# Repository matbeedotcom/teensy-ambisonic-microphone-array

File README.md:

# Teensy Ambisonic Microphone Array

A real-time 3D audio capture and direction-of-arrival (DOA) system using Teensy 4.1 and MEMS microphones.

## Overview

This project implements an 8-channel tetrahedral microphone array for spatial audio applications. Four INMP441 digital MEMS microphones capture sound from all directions, enabling real-time sound source localization with visual feedback.

### Key Features

- **8-channel audio capture** via dual Teensy 4.1 boards (master/slave configuration)
- **Real-time DOA estimation** using GCC-PHAT and SRP-PHAT algorithms
- **Sound classification** to filter and track specific audio types (voice, music, claps)
- **Live visualization** with 2D/3D directional plots and channel monitoring
- **3D-printable frame** with integrated wire management

## System Architecture

```
┌─────────────┐     I2S      ┌──────────────┐     USB Audio    ┌──────────────┐
│ 4x INMP441  ├─────────────►│ Master Teensy├────────────────►│              │
│ Microphones │              │     4.1      │                  │   Host PC    │
└─────────────┘              └──────┬───────┘                  │   (Python)   │
                                     │ TDM                      │              │
┌─────────────┐     I2S      ┌──────┴───────┐                  │ ┌──────────┐ │
│ 4x INMP441  ├─────────────►│ Slave Teensy │                  │ │   DOA    │ │
│ Microphones │              │     4.1      │                  │ │Processing│ │
└─────────────┘              └──────────────┘                  │ └──────────┘ │
                                                                └──────────────┘
```

## Hardware Requirements

- 2× Teensy 4.1 boards
- 8× INMP441 I2S MEMS microphone breakout boards
- 3D printer for tetrahedral frame (70.7mm edge length)
- Wire for I2S and TDM connections
- USB cables for power and data

## Quick Start

### 1. Assemble Hardware

Print the tetrahedral frame and mount microphones:
```bash
cd mechanical
python generate_stl.py  # Creates STL files for 3D printing
```

Follow the [assembly guide](mechanical/assembly_instructions.md) for wiring details.

### 2. Flash Firmware

Upload firmware to both Teensy boards:
- **Master**: `teensy_src/teensy_ambisonic_microphone.ino`
- **Slave**: `teensy_src/slave.ino`

Note: Requires [Teensyduino](https://www.pjrc.com/teensy/teensyduino.html) with USB descriptor patches from `teensy_src/patches/`.

### 3. Install Host Software

```bash
cd host_src
pip install -r requirements.txt
```

### 4. Run DOA Visualization

```bash
python doa_visualizer.py
```

Click "Start" to begin real-time sound source tracking.

## Features in Detail

### Direction of Arrival Algorithms

- **GCC-PHAT**: Fast cross-correlation for time-delay estimation
- **SRP-PHAT**: Robust beamforming-based localization
- **Least-Squares**: Traditional triangulation from time differences

### Sound Classification

Automatically identifies and filters:
- Human voice
- Music
- Claps/transients
- Whistles
- Background noise

### Array Geometry

Regular tetrahedron configuration:
- 43.3mm radius (center to vertex)
- 109.5° angular separation between microphones
- Omnidirectional coverage with minimal blind spots

## Project Structure

```
teensy_ambisonic_microphone/
├── teensy_src/        # Teensy firmware (master/slave)
├── host_src/          # Python DOA processing and visualization
├── mechanical/        # 3D-printable frame design (OpenSCAD)
└── pcb/              # KiCad PCB designs
```

## Performance

- **Sample rate**: 44.1 kHz
- **Latency**: ~23ms (1024 sample blocks)
- **Angular resolution**: 5° grid spacing
- **Update rate**: 20 Hz visualization
- **Maximum trackable distance**: Limited by SNR, typically 3-5 meters indoors

## Applications

- Acoustic scene analysis
- Smart home voice control
- Robotics navigation
- Virtual reality audio
- Acoustic research
- Educational demonstrations

## Contributing

Contributions welcome! Areas of interest:
- Multi-source tracking
- Beamforming implementation
- Raspberry Pi host support
- ROS integration

## License

MIT License - See LICENSE file for details

## Acknowledgments

Built with:
- [Teensy Audio Library](https://www.pjrc.com/teensy/td_libs_Audio.html)
- [INMP441 MEMS Microphones](https://invensense.tdk.com/products/digital/inmp441/)
- Scientific Python stack (NumPy, SciPy, Matplotlib)

## Resources

- [Direction of Arrival Estimation](https://en.wikipedia.org/wiki/Direction_of_arrival)
- [Ambisonic Audio](https://en.wikipedia.org/wiki/Ambisonics)
- [GCC-PHAT Algorithm](https://doi.org/10.1109/TASSP.1976.1162830)

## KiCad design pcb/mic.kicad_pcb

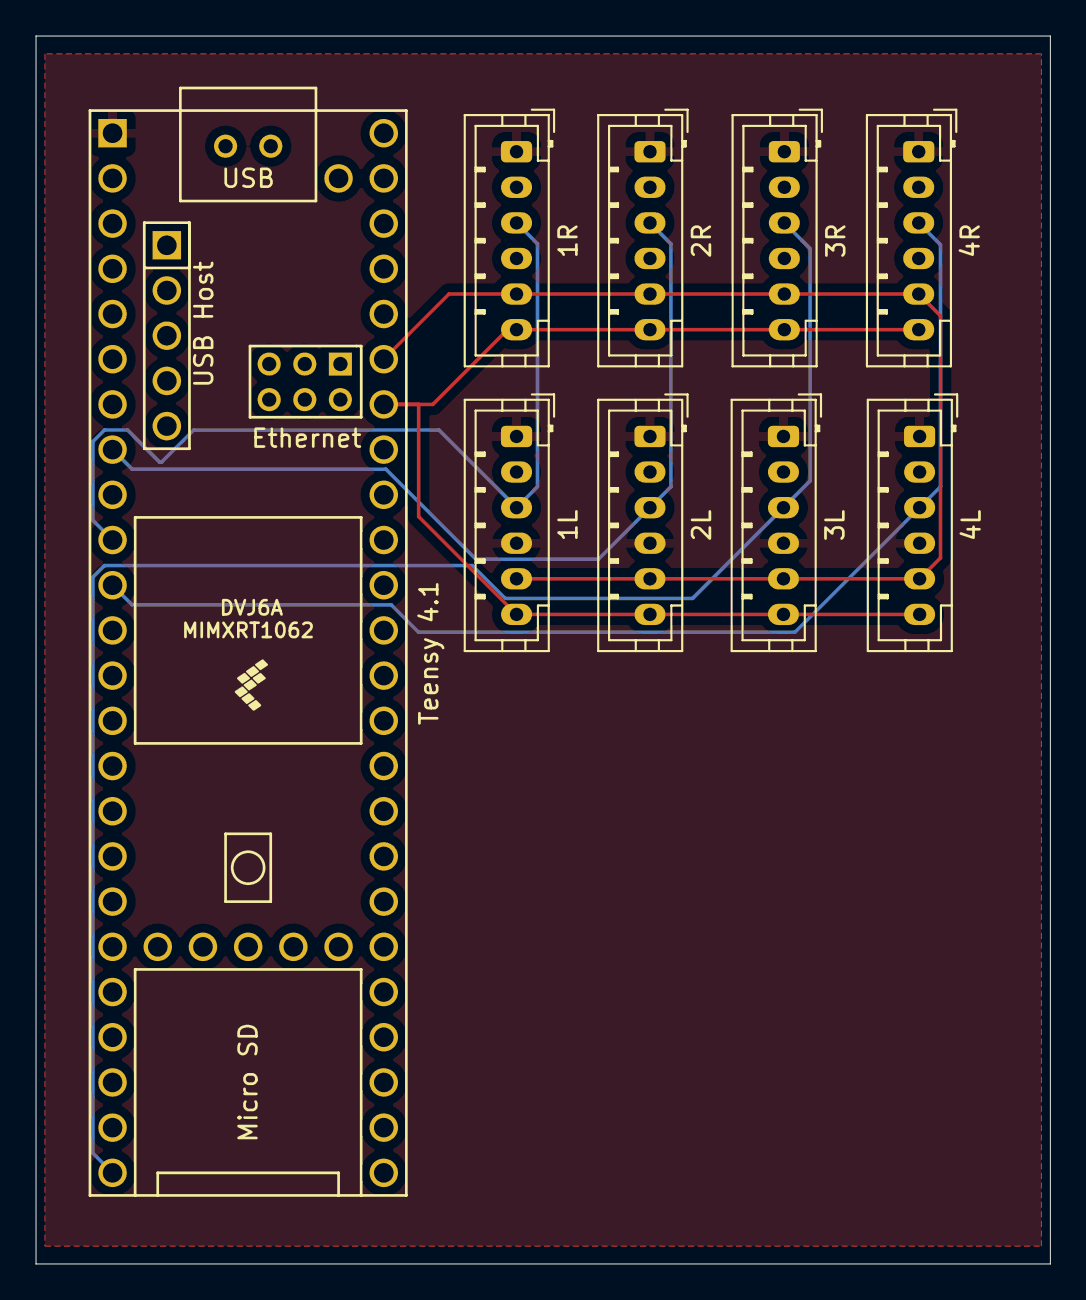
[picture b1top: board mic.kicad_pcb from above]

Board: 4 copper layers, 57.0 x 69.0 mm, 9 parts (0 on the bottom side), 8 nets.

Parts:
1L, 2L, 3L, 4L: LeftMic; JST_PH_B6B-PH-K_1x06_P2.00mm_Vertical
1R, 2R, 3R, 4R: RightMic; JST_PH_B6B-PH-K_1x06_P2.00mm_Vertical
Teensy 4.1: Teensy4.1; Teensy41

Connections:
+3.3V: 1L.2, 1R.2, 1R.4, 2L.2, 2R.2, 2R.4, 3L.2, 3R.2, 3R.4, 4L.2, 4R.2, 4R.4, Teensy 4.1.46 (3V3)
BCLK1: 1L.5, 1R.5, 2L.5, 2R.5, 3L.5, 3R.5, 4L.5, 4R.5, Teensy 4.1.43 (21_A7_RX5_BCLK1)
GND: 1L.1, 1L.4, 1R.1, 2L.1, 2L.4, 2R.1, 3L.1, 3L.4, 3R.1, 4L.1, 4L.4, 4R.1, Teensy 4.1.1 (GND)
LRCLK1: 1L.6, 1R.6, 2L.6, 2R.6, 3L.6, 3R.6, 4L.6, 4R.6, Teensy 4.1.42 (20_A6_TX5_LRCLK1)
SAI1_RXD0: 1L.3, 1R.3, Teensy 4.1.10 (8_TX2_IN1)
SAI1_RXD1: 2L.3, 2R.3, Teensy 4.1.8 (6_OUT1D)
SAI1_RXD2: 3L.3, 3R.3, Teensy 4.1.24 (32_OUT1B)
SAI1_RXD3: 4L.3, 4R.3, Teensy 4.1.11 (9_OUT1C)

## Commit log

2025-09-24 Current state
2025-09-24 Current working state
2025-09-25 Visualizer updated
2025-09-25 Update array geometry and enhance DOA visualizer with sound classification features
2025-09-25 Add README.md for Teensy Ambisonic Microphone Array project with detailed overview, features, system architecture, hardware requirements, quick start guide, and applications
2025-09-27 test
2025-09-27 Add con_pots_obj structure and integrate pots connector in DOA processing. Update audio capture initialization for buffer alignment and enhance debug logging. Modify SSL configuration for minimal pro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
2025-09-30 Implement initial setup for ODAS-Py, including CMake configuration, Python bindings, and build scripts for Windows. Add comprehensive documentation covering installation, usage, and audio capture fea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
2025-09-30 Refactor ODAS-Py structure by removing Windows-specific files and directories, including build scripts, audio capture source files, and configuration headers. Introduce new STL file for tetrahedron f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
2025-10-01 Add desktop mount for parametric spherical microphone array
    This commit introduces a new SCAD file for a desktop mount designed to securely attach the ambisonic microphone array to a desktop surface. Key features include a stable circular base, a vertical sup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
